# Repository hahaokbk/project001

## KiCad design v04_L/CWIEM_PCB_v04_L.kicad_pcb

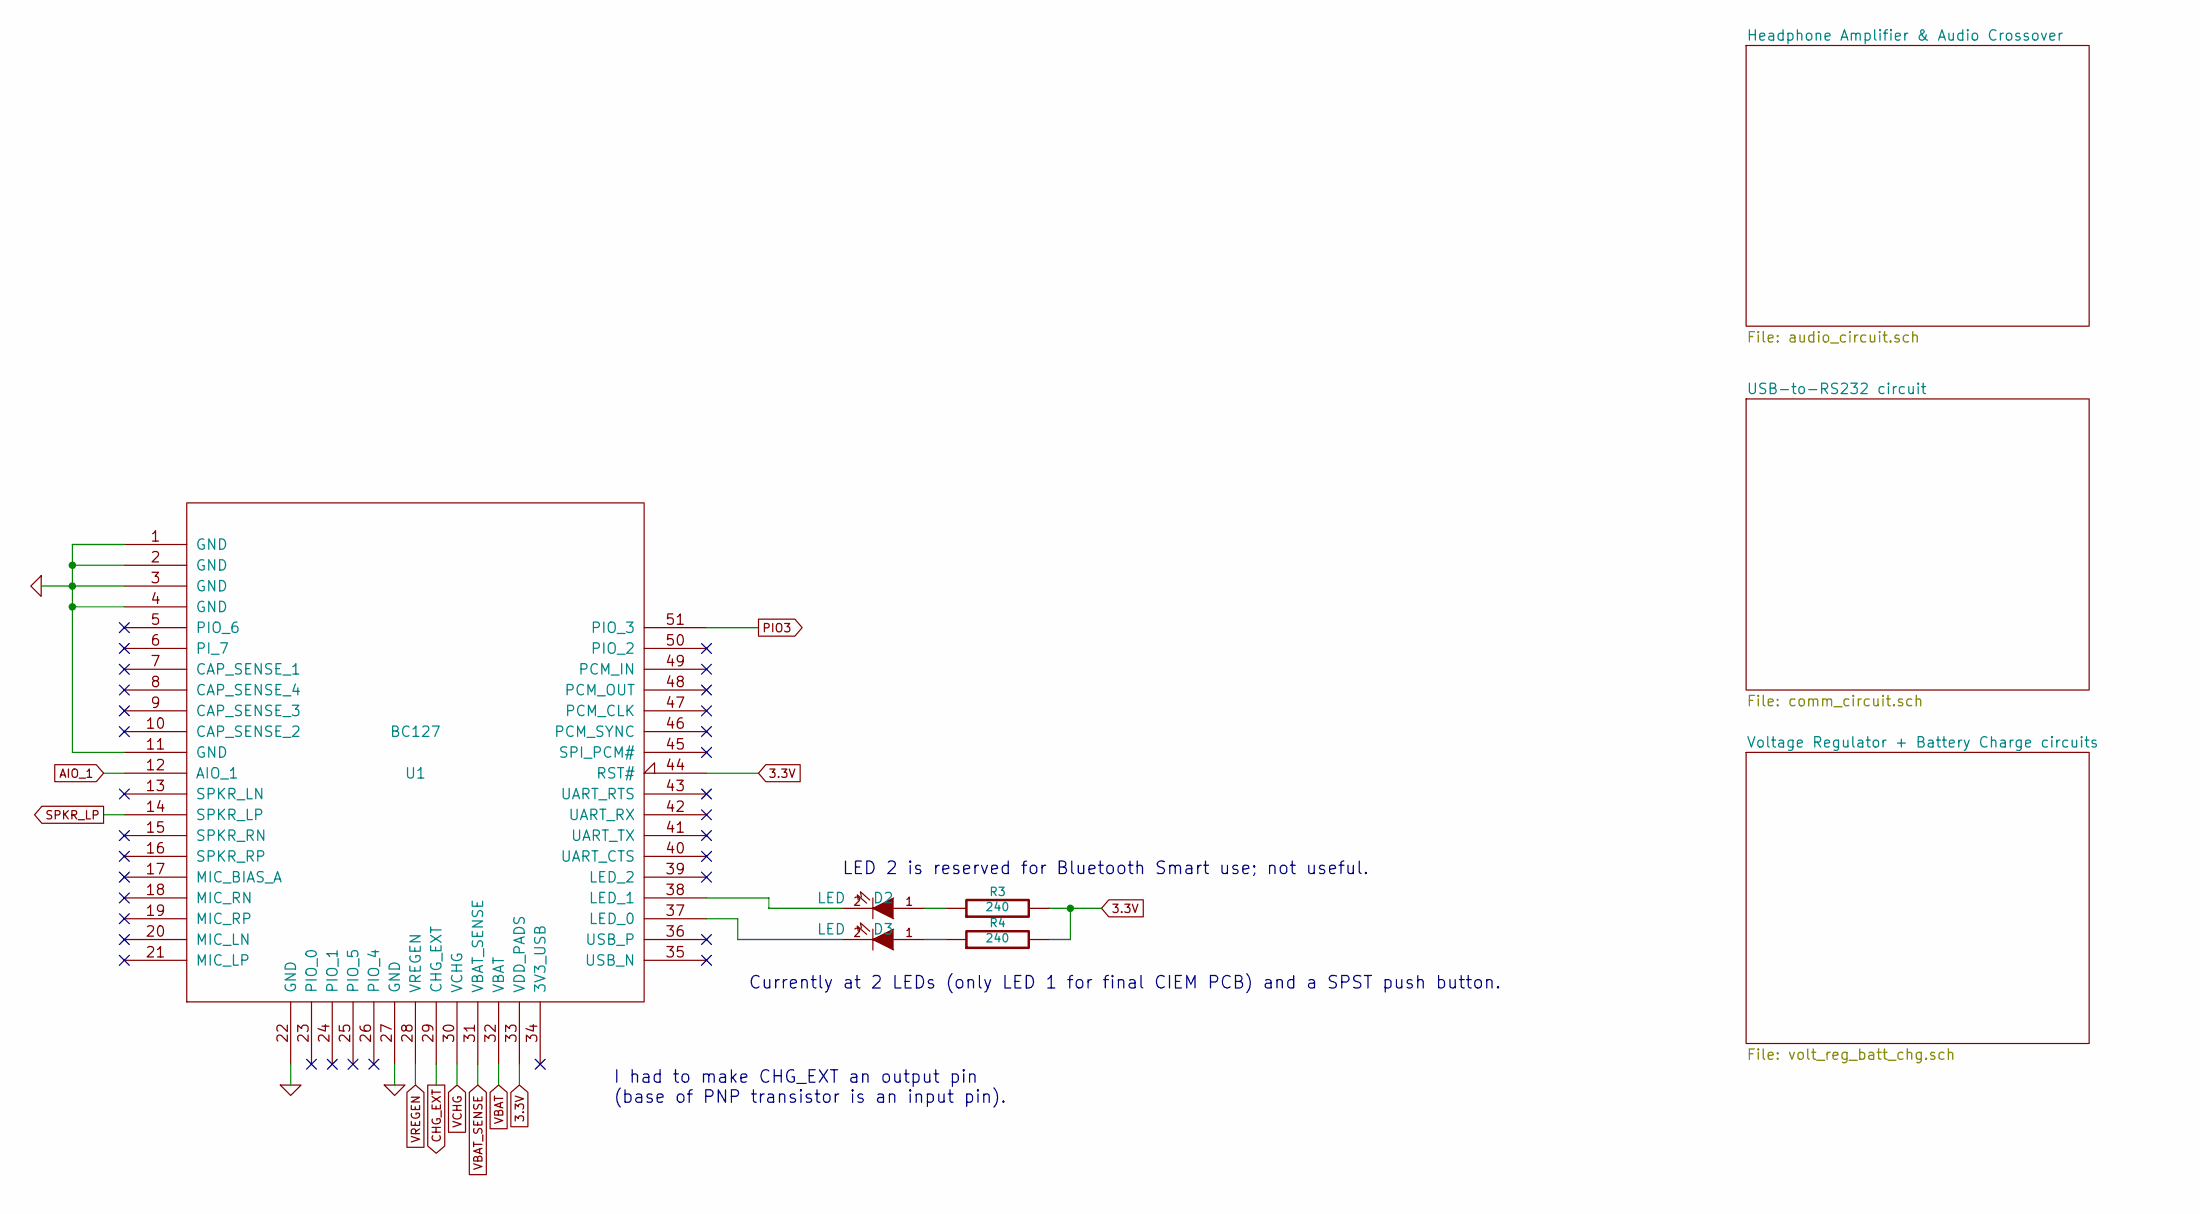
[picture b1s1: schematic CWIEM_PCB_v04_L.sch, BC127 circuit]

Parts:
D2, D3: LED
R3, R4: 240
U1: BC127; MODULE

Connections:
3.3V: R3.2, R4.2, U1.33 (VDD_PADS), U1.44 (RST#); also elsewhere on the board
5V_USB: U1.30 (VCHG); also elsewhere on the board
AIO_1: U1.12 (AIO_1); also elsewhere on the board
CHG_EXT: U1.29 (CHG_EXT); also elsewhere on the board
GND: U1.1 (GND), U1.2 (GND), U1.3 (GND), U1.4 (GND), U1.11 (GND), U1.22 (GND), U1.27 (GND); also elsewhere on the board
unnamed: D2.2 (K), U1.38 (LED_1)
unnamed: D3.2 (K), U1.37 (LED_0)
unnamed: D2.1 (A), R3.1
unnamed: D3.1 (A), R4.1
PIO3: U1.51 (PIO_3); also elsewhere on the board
SPKR_LP: U1.14 (SPKR_LP); also elsewhere on the board
VBAT: U1.32 (VBAT); also elsewhere on the board
VBAT_SENSE: U1.31 (VBAT_SENSE); also elsewhere on the board
VREGEN: U1.28 (VREGEN); also elsewhere on the board

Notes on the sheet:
Currently at 2 LEDs (only LED 1 for final CIEM PCB) and a SPST push button.
I had to make CHG_EXT an output pin (base of PNP transistor is an input pin).
LED 2 is reserved for Bluetooth Smart use; not useful.

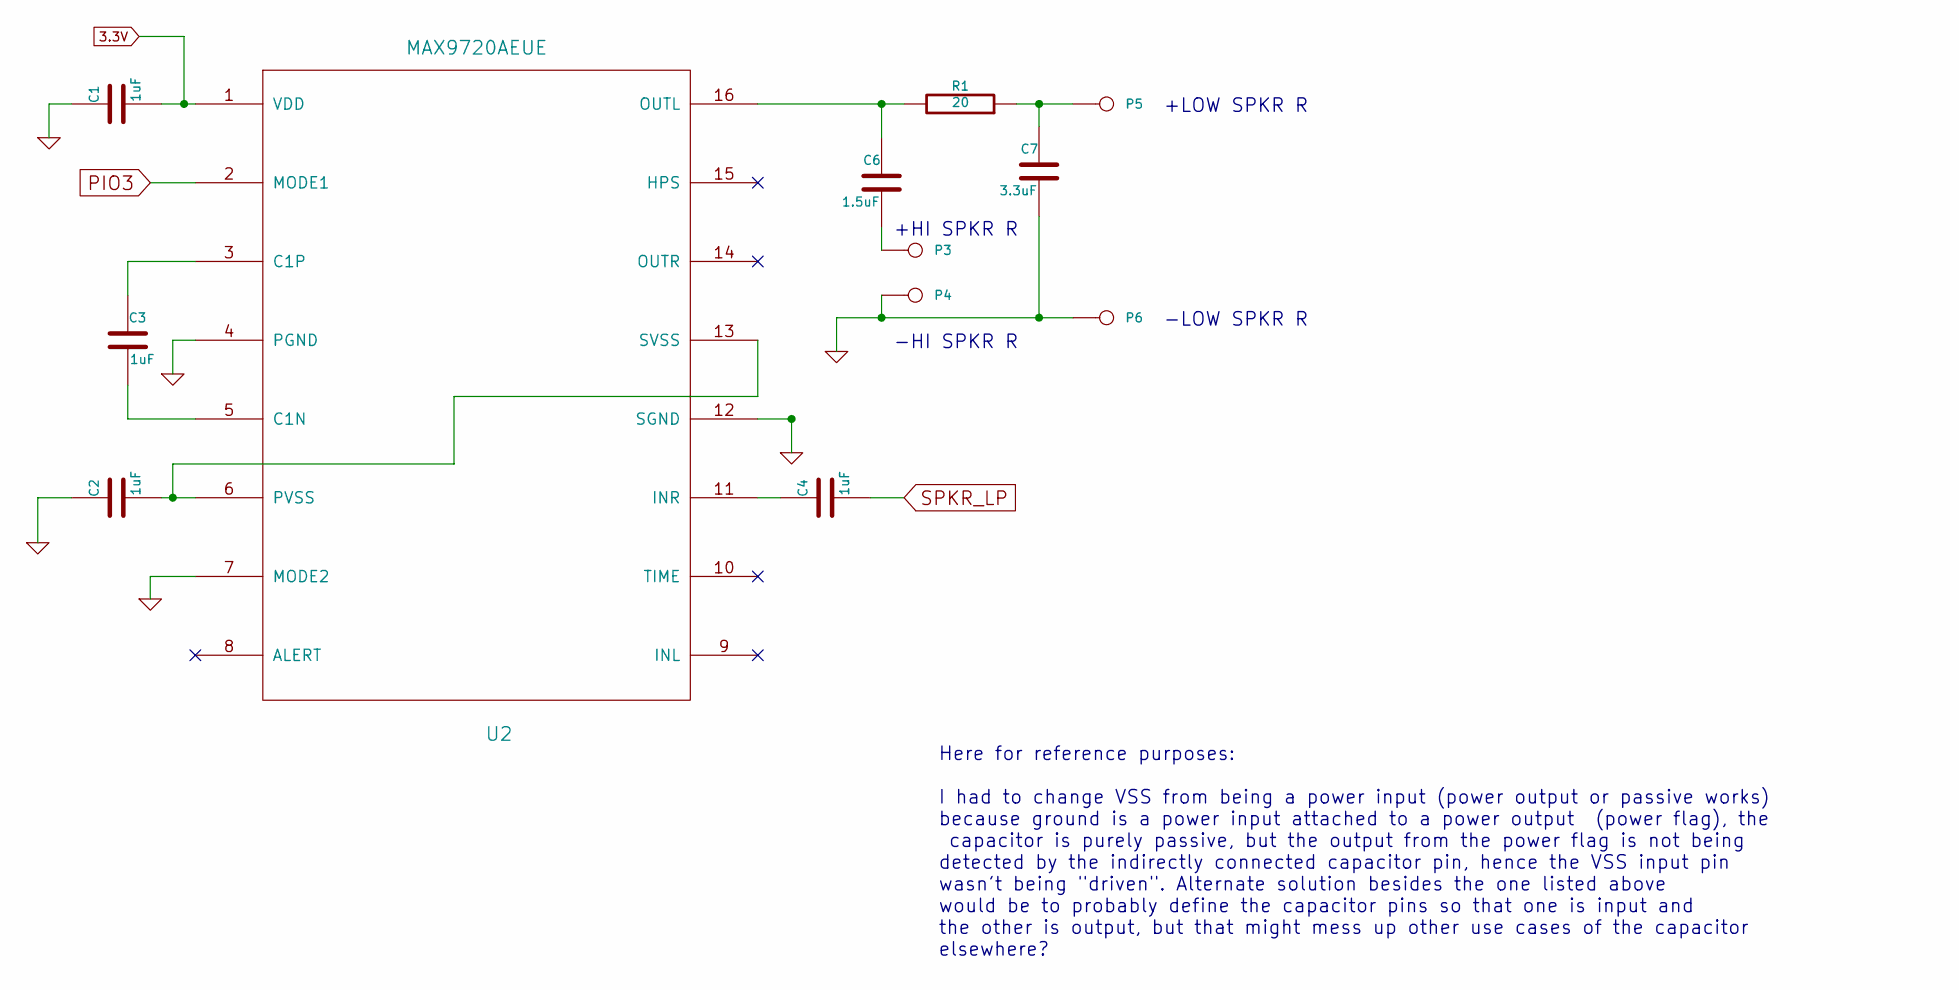
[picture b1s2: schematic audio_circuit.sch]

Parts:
C1, C2, C3, C4: 1uF
C6: 1.5uF
C7: 3.3uF
P3, P4, P5, P6: CONN_1
R1: 20
U2: MAX9720AEUE

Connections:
3.3V: C1.2, U2.1 (VDD); also elsewhere on the board
GND: C1.1, C2.1, C7.2, P4.1, P6.1, U2.4 (PGND), U2.7 (MODE2), U2.12 (SGND); also elsewhere on the board
unnamed: C3.2, U2.5 (C1N)
unnamed: C3.1, U2.3 (C1P)
unnamed: C6.2, P3.1
unnamed: C6.1, R1.2, U2.16 (OUTL)
unnamed: C7.1, P5.1, R1.1
unnamed: C4.1, U2.11 (INR)
unnamed: C2.2, U2.6 (PVSS), U2.13 (SVSS)
PIO3: U2.2 (MODE1); also elsewhere on the board
SPKR_LP: C4.2; also elsewhere on the board

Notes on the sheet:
Here for reference purposes: I had to change VSS from being a power input (power output or passive works) because ground is a power input attached to a power output (power flag), the capacitor is purely passive, but the output from the power flag is not being detected by the indirectly connected ca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
+LOW SPKR R
-LOW SPKR R
+HI SPKR R
-HI SPKR R

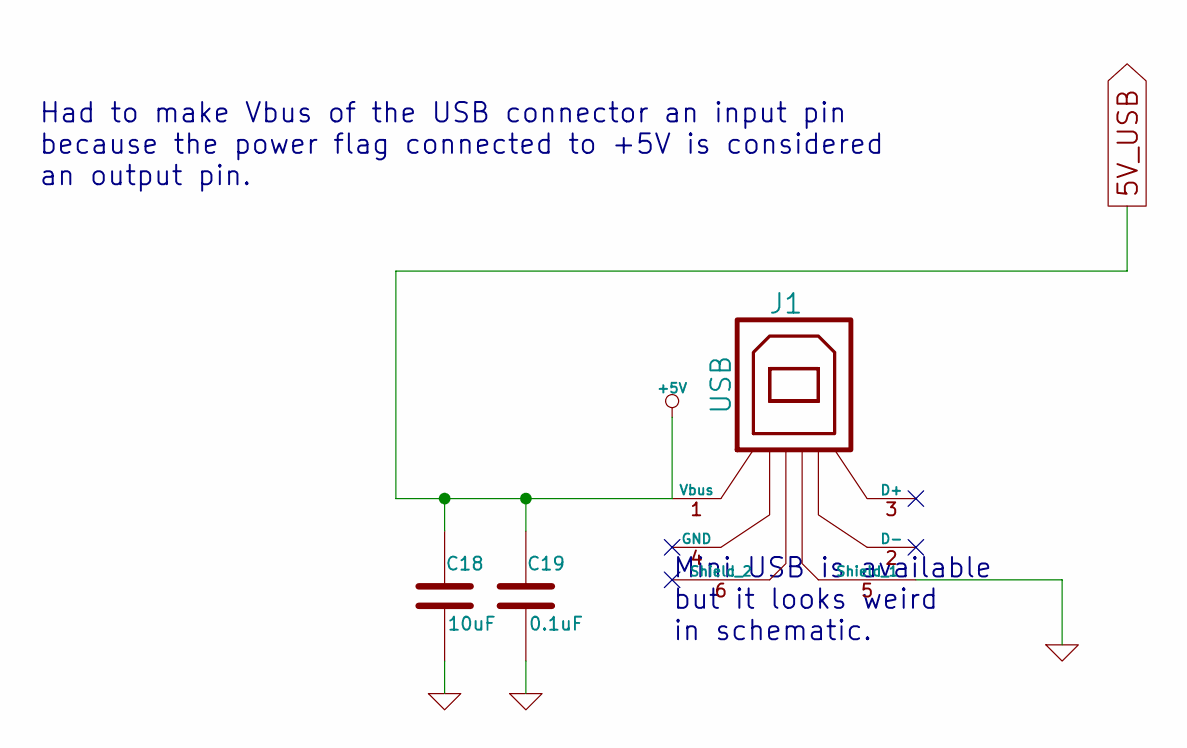
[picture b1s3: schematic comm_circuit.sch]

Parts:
C18: 10uF
C19: 0.1uF
J1: USB

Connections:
5V_USB: C18.1, C19.1, J1.1 (Vbus); also elsewhere on the board
GND: C18.2, C19.2, J1.5 (Shield_1); also elsewhere on the board

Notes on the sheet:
Mini USB is available but it looks weird in schematic.
Had to make Vbus of the USB connector an input pin because the power flag connected to +5V is considered an output pin.

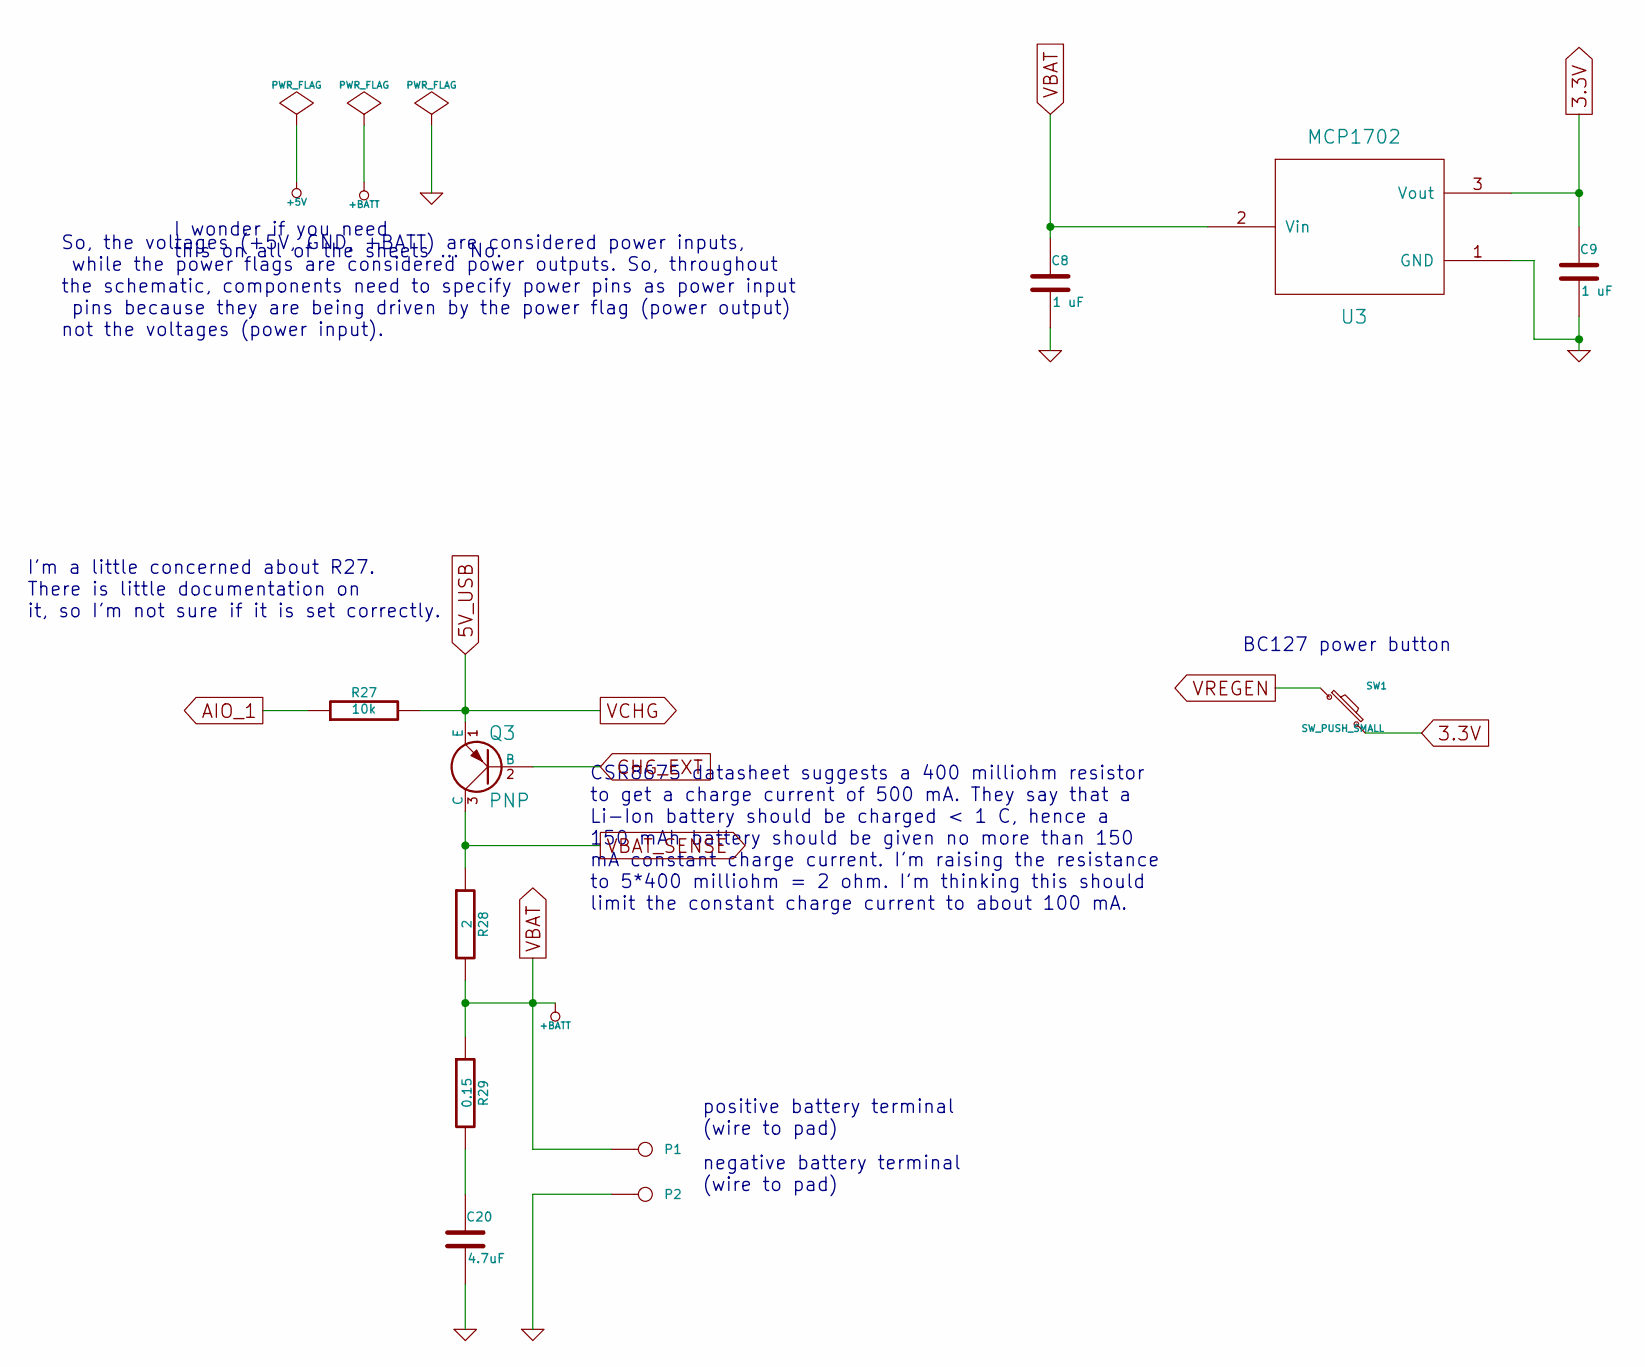
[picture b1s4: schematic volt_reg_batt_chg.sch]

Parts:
C8, C9: 1 uF
C20: 4.7uF
P1, P2: CONN_1
Q3: PNP
R27: 10k
R28: 2
R29: 0.15
SW1: SW_PUSH_SMALL
U3: MCP1702

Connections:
3.3V: C9.1, SW1.2, U3.3 (Vout); also elsewhere on the board
5V_USB: Q3.1 (E), R27.2; also elsewhere on the board
AIO_1: R27.1; also elsewhere on the board
CHG_EXT: Q3.2 (B); also elsewhere on the board
GND: C8.2, C9.2, C20.2, P2.1, U3.1 (GND); also elsewhere on the board
unnamed: C20.1, R29.2
VBAT: C8.1, P1.1, R28.2, R29.1, U3.2 (Vin); also elsewhere on the board
VBAT_SENSE: Q3.3 (C), R28.1; also elsewhere on the board
VREGEN: SW1.1; also elsewhere on the board

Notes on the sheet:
I wonder if you need this on all of the sheets ... No.
So, the voltages (+5V, GND, +BATT) are considered power inputs, while the power flags are considered power outputs. So, throughout the schematic, components need to specify power pins as power input pins because they are being driven by the power flag (power output) not the voltages (power input).
positive battery terminal (wire to pad)
negative battery terminal (wire to pad)
BC127 power button
I'm a little concerned about R27. There is little documentation on it, so I'm not sure if it is set correctly.
CSR8675 datasheet suggests a 400 milliohm resistor to get a charge current of 500 mA. They say that a Li-Ion battery should be charged < 1 C, hence a 150 mAh battery should be given no more than 150 mA constant charge current. I'm raising the resistance to 5*400 milliohm = 2 ohm. I'm thinking this 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

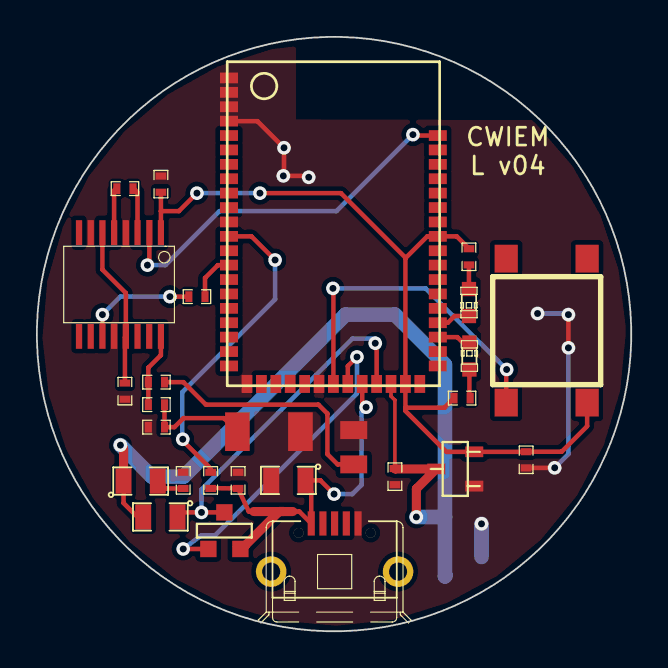
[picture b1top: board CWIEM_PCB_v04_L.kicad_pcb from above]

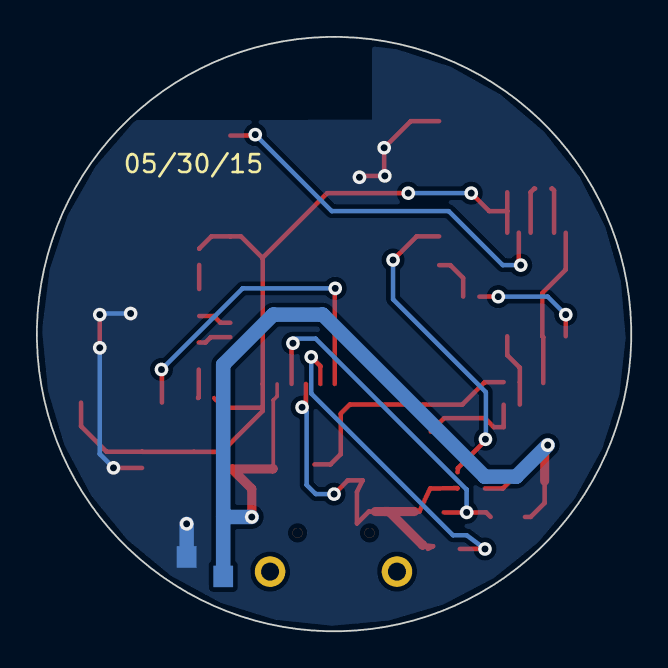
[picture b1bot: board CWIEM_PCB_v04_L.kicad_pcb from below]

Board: 2 copper layers, 33.0 x 33.0 mm, 31 parts (2 on the bottom side), 22 nets.

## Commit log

2014-10-18 adding current (10/18/14 1:55 PM) project versions
2014-10-18 Basically just added a single DIP switch to battery charging circuit.
2014-10-25 ERC.
2014-10-25 Create pre-revprop-change.bat
    Creating this server-side "hook" to allow me to edit log comment client-side. Hopefully this works. if not, fuck this bullshit.
2014-10-25 updates:
    1) added DIP-1 switch to connect/disconnect battery
    2) annotated components in the entire schematic
    3) generated netlist for the schematic
    4) matched components with footprints (caps, DIP switch, diodes, LEDs, I think that's it ...)
2014-12-07 Created BC127 footprint. Associated BC127 component with its footprint. Update to footprint associations.
2015-01-16 Updating with latest edits (haven't committed in a while)
2015-01-16 Splitting v01 (stereo headphone PCB) to v01_R (right headphone PCB)
2015-01-16 Splitting v01 (stereo headphone PCB) to v01_L (left headphone PCB)
2015-01-16 Updating "v01" to "v01_L"
2015-01-16 Changing "v01" to "v01_R"
2015-01-16 Update includes removing right side of audio circuit
2015-01-16 Update removes the left channel of the audio circuit.
2015-01-17 Updating entire schematic and footprint selections. Adding jst-ph footprints.
2015-01-20 Adding very rough initial version of PCB. The BA driver pads were not exact yet (based off of a Sonion driver datasheet).
2015-01-20 Adding balanced armature driver pad and a module library with a SMD pushbutton.
2015-01-20 The rough initial version of the PCB.
2015-01-25 Update with 2.00" diameter version of the CWIEM R v01 PCB. The only change remaining was to finalize sound driver pad placement and sizing. After that, production files could be generated for board m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
2015-01-31 Updating with CWIEM R v01 (1.8 inch diameter edition)
2015-01-31 Adding some audio speaker pad footprints and micro B USB footprint
2015-01-31 Updating PCB silkscreen (some part numbers were under the parts) and adding a zipped folder with first PCB files for order.
2015-02-26 Adding CWIEM v02 (left) -- goal is to fit design on 1.3" diameter circular PCB
2015-02-26 Adding CWIEM v02 (right) -- the goal is to fit the v01 design onto a 1.3-inch diameter PCB
2015-02-28 Adding TE Connectivity Micro USB PCB footprint
2015-02-28 Update -- order submitted to OSHPark
2015-03-24 Modifying micro USB port drill hole dimensions and distance
2015-03-24 Just submitting whatever I last changed.
2015-03-24 Submitting design CWIEM PCB R v03.
    Changelog:
    1) (pcb) remove extra tracks for pushbutton
    2) (module editor) fix usb port drill dimensions
    3) (schematic/pcb) connect VCHG pin
    4) (schematic/pcb) connect MUTE pin
    5) (pcb) replace battery connector pads
2015-03-24 Submitting the latest stuff.
2015-04-13 Adding CWIEM PCB R v04 -- adds a power-efficient voltage regulator, adds a power-efficient headphone driver, and corrects for USB ground issue
2015-06-05 Adding CWIEM BCB L v04
2015-06-16 Add CWIEM PCB v05
2015-07-22 Updating module
